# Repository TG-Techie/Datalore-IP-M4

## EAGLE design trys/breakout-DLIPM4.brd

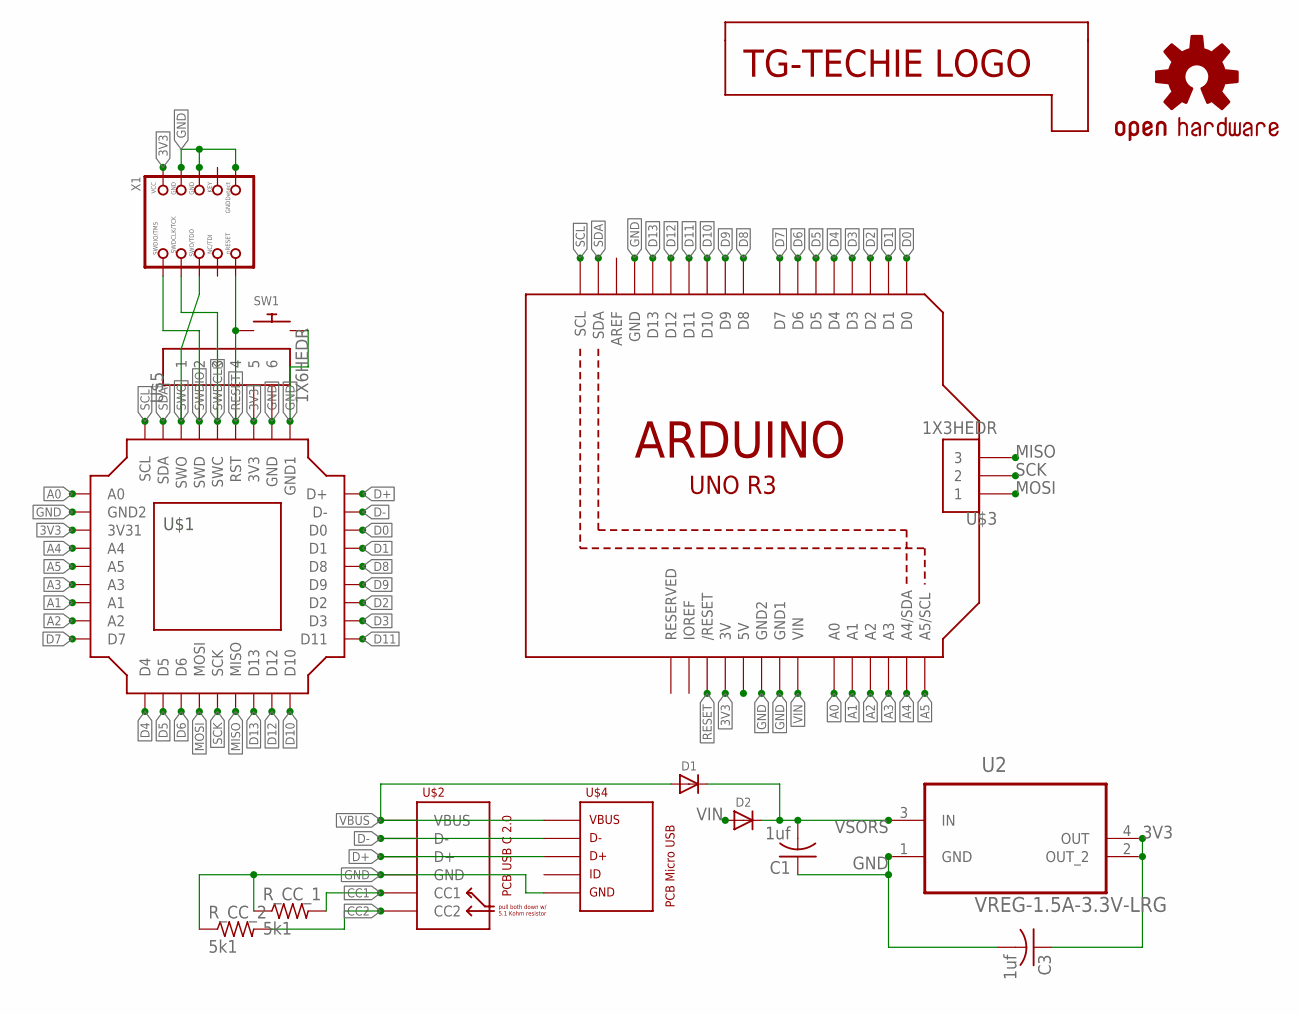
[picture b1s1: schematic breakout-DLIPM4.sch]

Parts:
C1, C3: 1uf; TG-C0805MP
D1, D2: DIODESOD-123; SOD-123
LOGO1: OSHW-LOGOS; OSHW-LOGO-S
R_CC_1, R_CC_2: 5k1; TG-R0805
SW1: SWITCH_PUSHBUTTONEVQ-PE; TACT_PANA-EVQ
U1: ARDUINOR3-DIMENSION; ARDUINOR3
U2: VREG-1.5A-3.3V-LRG; SOT230P700X180-4N
U$1: DATALORE-IP-M4; DL_IP_36-.1IN-FOOTPRINT
U$2: USB-C-PCB-USB-2.0-TYPE-CDS_2; USB_TYPE_C_DS_2
U$3: 1X3HEDR; 1X3_HEDR
U$4: USB-B-PCB-MICRO_BSS_2; USB_TYPE_B_SS_2
U$5: 1X6HEDR; 1X6_HEDR
U$7: LOGO-TG_TECHIEBIG?; LOGO_TG_TEST_LARGE
X1: CON-SWD-JTAG-CORTEXBOXPOSTS; 2X05_1.27MM_BOX_POSTS

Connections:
3V3: C3.1, U1.3V, U2.2 (OUT_2), U2.4 (OUT), U$1.7 (3V3), U$1.34 (3V31), U$5.5, X1.1 (VCC)
A0: U1.A0, U$1.36 (A0)
A1: U1.A1, U$1.30 (A1)
A2: U1.A2, U$1.29 (A2)
A3: U1.A3, U$1.31 (A3)
A4: U1.A4 (A4/SDA), U$1.33 (A4)
A5: U1.A5 (A5/SCL), U$1.32 (A5)
CC1: R_CC_1.2, U$2.A5 (CC1)
CC2: R_CC_2.2, U$2.B5 (CC2)
D0: U1.D0, U$1.12 (D0)
D1: U1.D1, U$1.13 (D1)
D2: U1.D2, U$1.16 (D2)
D3: U1.D3, U$1.17 (D3)
D4: U1.D4, U$1.27 (D4)
D5: U1.D5, U$1.26 (D5)
D6: U1.D6, U$1.25 (D6)
D7: U1.D7, U$1.28 (D7)
D8: U1.D8, U$1.14 (D8)
D9: U1.D9, U$1.15 (D9)
D10: U1.D10, U$1.19 (D10)
D11: U1.D11, U$1.18 (D11)
D12: U1.D12, U$1.20 (D12)
D13: U1.D13, U$1.21 (D13)
D+: U$1.10 (D+), U$2.A6 (D+), U$2.B6 (D+), U$4.3
D-: U$1.11 (D-), U$2.A7 (D-), U$2.B7 (D-), U$4.2
GND: C1.1, C3.2, R_CC_1.1, R_CC_2.1, SW1.P$2, U1.GND, U1.GND1, U1.GND2, U2.1 (GND), U$1.8 (GND), U$1.9 (GND1), U$1.35 (GND2), U$2.A1 (GND), U$2.A12 (GND), U$2.B1 (GND), U$2.B12 (GND), U$4.5, U$5.6, X1.3 (GND), X1.5 (GND), X1.9 (GNDDETECT)
MISO: U$1.22 (MISO), U$3.3
MOSI: U$1.24 (MOSI), U$3.1
RESET: SW1.P$1, U1.RESET (/RESET), U$1.6 (RST), U$5.4, X1.10 (NRESET)
SCK: U$1.23 (SCK), U$3.2
SCL: U1.SCL, U$1.1 (SCL)
SDA: U1.SDA, U$1.2 (SDA)
SWDCLK: U$1.5 (SWC), U$5.3, X1.4 (SWDCLK)
SWDIO: U$1.4 (SWD), U$5.2, X1.2 (SWDIO)
SWO: U$1.3 (SWO), U$5.1, X1.6 (SWO)
VBUS: D1.A, U$2.A4 (VBUS), U$2.A9 (VBUS), U$2.B4 (VBUS), U$2.B9 (VBUS), U$4.1
VIN: D2.A, U1.VIN
VSORS: C1.2, D1.C, D2.C, U2.3 (IN)

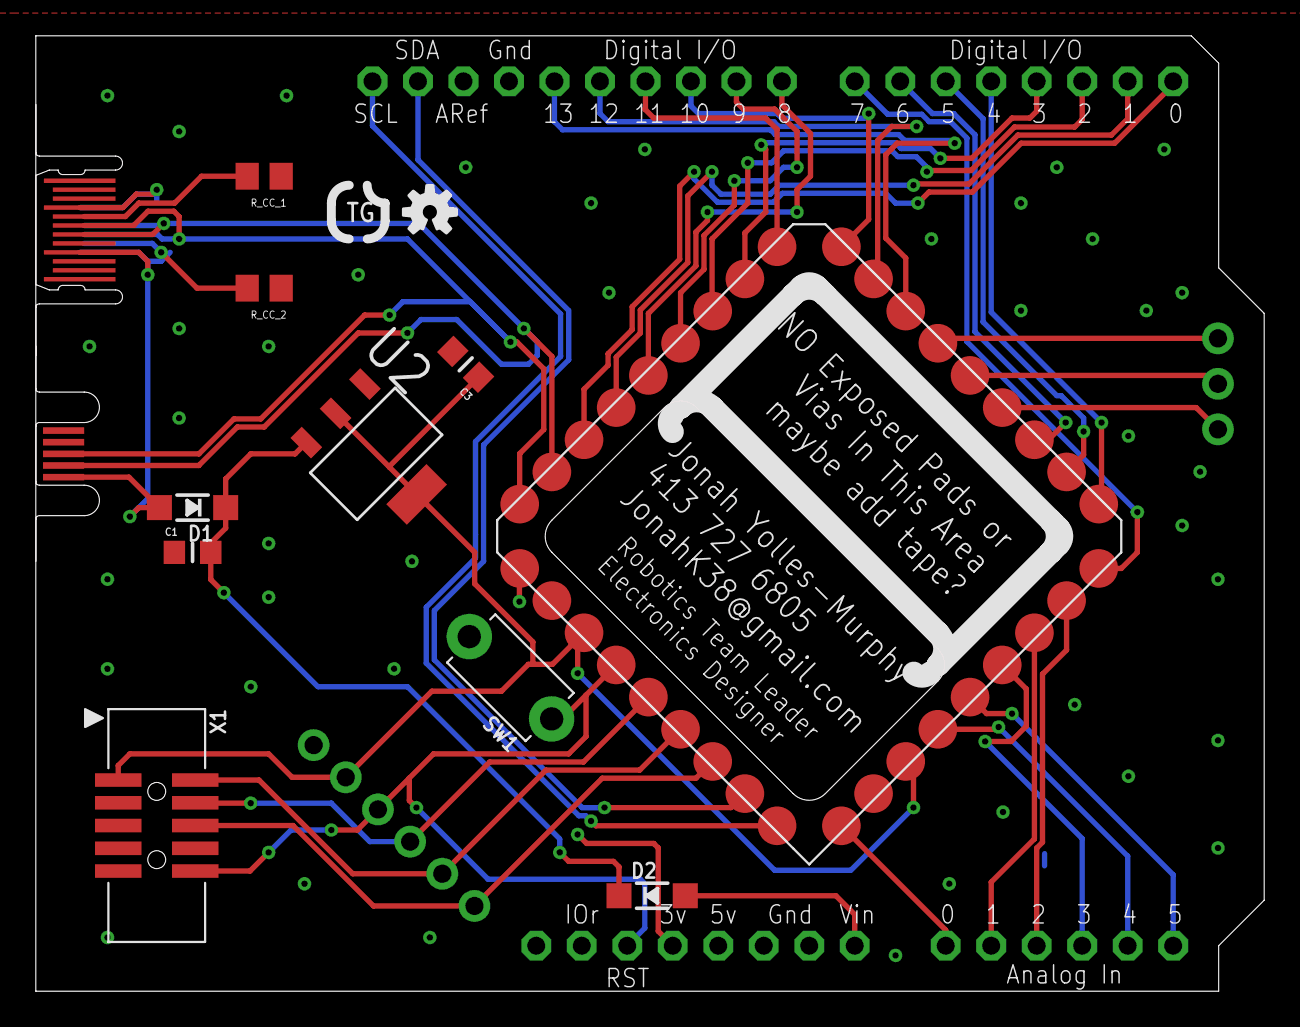
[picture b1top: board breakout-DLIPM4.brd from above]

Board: 2 copper layers, 68.6 x 53.3 mm, 17 parts (0 on the bottom side), 38 nets.

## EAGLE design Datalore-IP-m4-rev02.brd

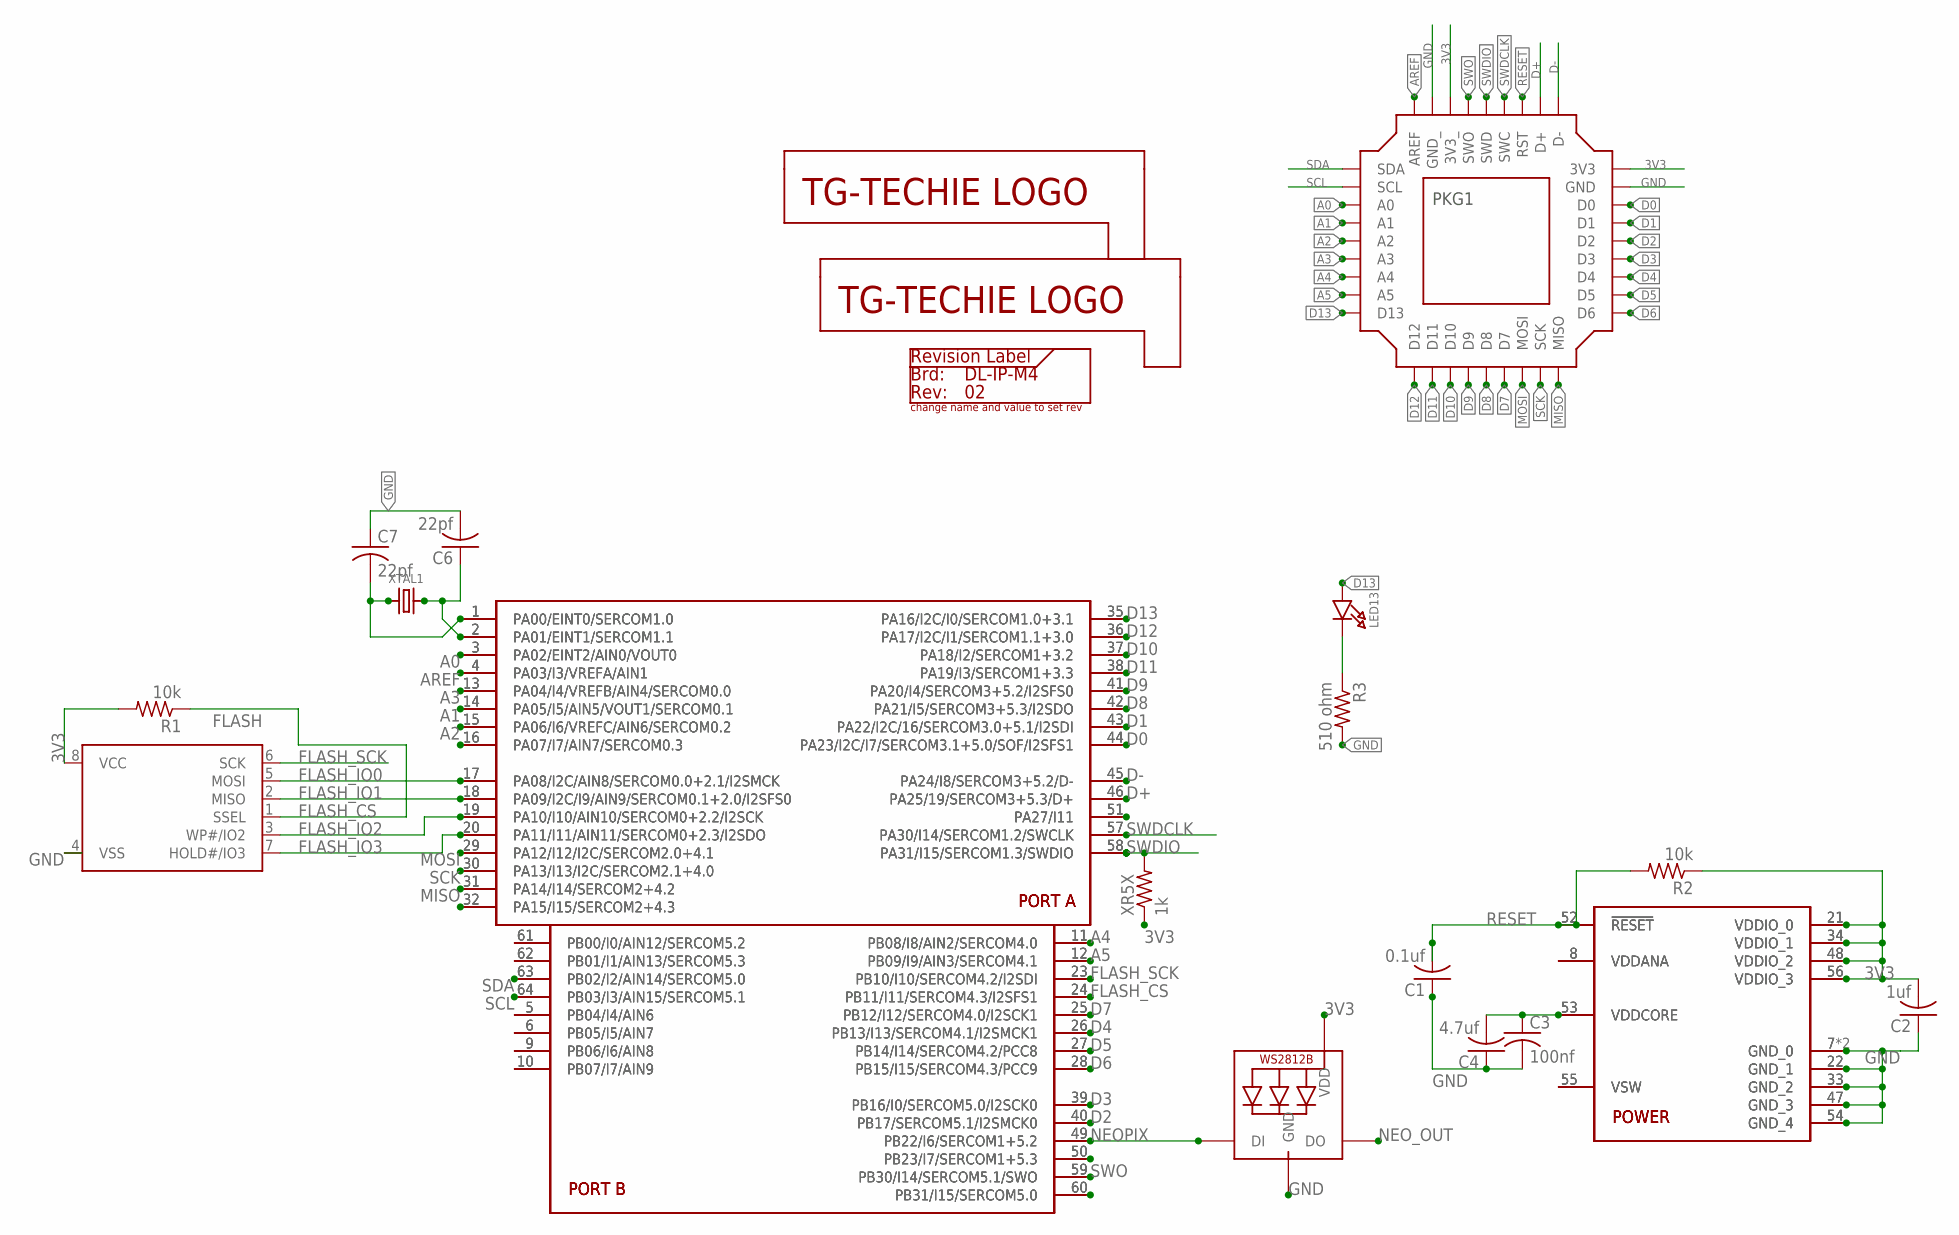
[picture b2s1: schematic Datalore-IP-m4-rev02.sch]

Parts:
..: MCU-ATSAMD51J-ADA+TG_TQFP; QFP50P1200X1200X120-64N
C1: 0.1uf; TG-0603
C2: 1uf; TG-0603
C3: 100nf; TG-0603
C4: 4.7uf; TG-0603
C6, C7: 22pf; TG-0603
DL-IP-M4: 02; REVISION_LABEL
FLASH: FLASH-SPI-CIRCUIT_PYTHON150MIL; SOIC8_150MIL
LED1: LED-NEO-WS2812B3535; LED3535
LED13: LED-MICROBUILDER1206_NOOUTLINE; MICROBUILDER_CHIPLED_1206_NOOUTLINE
PKG1: DATALORE_IP_M4PACKAGE; DL_IP_36-100MIL-PACKAGE
R1, R2: 10k; TG-0603
R3: 510 ohm; TG-0603
U$1, U$5: LOGO-TG_TECHIEBIG?; LOGO_TG_TEST_LARGE
U$3: MCU-ATSAMD51J-ADA+TG_QFP_ADA; MICROBUILDER_PQFN64-1
XR5X: 1k; TG-0603
XTAL1: XTAL_ADA4.9X1.8; MICROBUILDER_CRYSTAL_4.9X1.8

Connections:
3V3: ...21 (VDDIO_0), ...34 (VDDIO_1), ...48 (VDDIO_2), ...56 (VDDIO_3), C2.2, FLASH.8 (VCC), LED1.2 (VDD), PKG1.3 (3V3_), PKG1.10 (3V3), R1.2, R2.1, U$3.21 (VDDIO_0), U$3.34 (VDDIO_1), U$3.48 (VDDIO_2), U$3.56 (VDDIO_3), XR5X.1
A0: ...3 (PA02/EINT2/AIN0/VOUT0), PKG1.34 (A0), U$3.3 (PA02/EINT2/AIN0/VOUT0)
A1: ...14 (PA05/I5/AIN5/VOUT1/SERCOM0.1), PKG1.33 (A1), U$3.14 (PA05/I5/AIN5/VOUT1/SERCOM0.1)
A2: ...15 (PA06/I6/VREFC/AIN6/SERCOM0.2), PKG1.32 (A2), U$3.15 (PA06/I6/VREFC/AIN6/SERCOM0.2)
A3: ...13 (PA04/I4/VREFB/AIN4/SERCOM0.0), PKG1.31 (A3), U$3.13 (PA04/I4/VREFB/AIN4/SERCOM0.0)
A4: ...11 (PB08/I8/AIN2/SERCOM4.0), PKG1.30 (A4), U$3.11 (PB08/I8/AIN2/SERCOM4.0)
A5: ...12 (PB09/I9/AIN3/SERCOM4.1), PKG1.29 (A5), U$3.12 (PB09/I9/AIN3/SERCOM4.1)
AREF: ...4 (PA03/I3/VREFA/AIN1), PKG1.1 (AREF), U$3.4 (PA03/I3/VREFA/AIN1)
D0: ...44 (PA23/I2C/I7/SERCOM3.1+5.0/SOF/I2SFS1), PKG1.12 (D0), U$3.44 (PA23/I2C/I7/SERCOM3.1+5.0/SOF/I2SFS1)
D1: ...43 (PA22/I2C/16/SERCOM3.0+5.1/I2SDI), PKG1.13 (D1), U$3.43 (PA22/I2C/16/SERCOM3.0+5.1/I2SDI)
D2: ...40 (PB17/SERCOM5.1/I2SMCK0), PKG1.14 (D2), U$3.40 (PB17/SERCOM5.1/I2SMCK0)
D3: ...39 (PB16/I0/SERCOM5.0/I2SCK0), PKG1.15 (D3), U$3.39 (PB16/I0/SERCOM5.0/I2SCK0)
D4: ...26 (PB13/I13/SERCOM4.1/I2SMCK1), PKG1.16 (D4), U$3.26 (PB13/I13/SERCOM4.1/I2SMCK1)
D5: ...27 (PB14/I14/SERCOM4.2/PCC8), PKG1.17 (D5), U$3.27 (PB14/I14/SERCOM4.2/PCC8)
D6: ...28 (PB15/I15/SERCOM4.3/PCC9), PKG1.18 (D6), U$3.28 (PB15/I15/SERCOM4.3/PCC9)
D7: ...25 (PB12/I12/SERCOM4.0/I2SCK1), PKG1.22 (D7), U$3.25 (PB12/I12/SERCOM4.0/I2SCK1)
D8: ...42 (PA21/I5/SERCOM3+5.3/I2SDO), PKG1.23 (D8), U$3.42 (PA21/I5/SERCOM3+5.3/I2SDO)
D9: ...41 (PA20/I4/SERCOM3+5.2/I2SFS0), PKG1.24 (D9), U$3.41 (PA20/I4/SERCOM3+5.2/I2SFS0)
D10: ...37 (PA18/I2/SERCOM1+3.2), PKG1.25 (D10), U$3.37 (PA18/I2/SERCOM1+3.2)
D11: ...38 (PA19/I3/SERCOM1+3.3), PKG1.26 (D11), U$3.38 (PA19/I3/SERCOM1+3.3)
D12: ...36 (PA17/I2C/I1/SERCOM1.1+3.0), PKG1.27 (D12), U$3.36 (PA17/I2C/I1/SERCOM1.1+3.0)
D13: ...35 (PA16/I2C/I0/SERCOM1.0+3.1), LED13.A, PKG1.28 (D13), U$3.35 (PA16/I2C/I0/SERCOM1.0+3.1)
D+: ...46 (PA25/19/SERCOM3+5.3/D+), PKG1.8 (D+), U$3.46 (PA25/19/SERCOM3+5.3/D+)
D-: ...45 (PA24/I8/SERCOM3+5.2/D-), PKG1.9 (D-), U$3.45 (PA24/I8/SERCOM3+5.2/D-)
FLASH_CS: ...24 (PB11/I11/SERCOM4.3/I2SFS1), FLASH.1 (SSEL), R1.1, U$3.24 (PB11/I11/SERCOM4.3/I2SFS1)
FLASH_IO0: ...17 (PA08/I2C/AIN8/SERCOM0.0+2.1/I2SMCK), FLASH.5 (MOSI), U$3.17 (PA08/I2C/AIN8/SERCOM0.0+2.1/I2SMCK)
FLASH_IO1: ...18 (PA09/I2C/I9/AIN9/SERCOM0.1+2.0/I2SFS0), FLASH.2 (MISO), U$3.18 (PA09/I2C/I9/AIN9/SERCOM0.1+2.0/I2SFS0)
FLASH_IO2: ...19 (PA10/I10/AIN10/SERCOM0+2.2/I2SCK), FLASH.3 (WP#/IO2), U$3.19 (PA10/I10/AIN10/SERCOM0+2.2/I2SCK)
FLASH_IO3: ...20 (PA11/I11/AIN11/SERCOM0+2.3/I2SDO), FLASH.7 (HOLD#/IO3), U$3.20 (PA11/I11/AIN11/SERCOM0+2.3/I2SDO)
FLASH_SCK: ...23 (PB10/I10/SERCOM4.2/I2SDI), FLASH.6 (SCK), U$3.23 (PB10/I10/SERCOM4.2/I2SDI)
GND: ...7 (GND_0), ...22 (GND_1), ...33 (GND_2), ...47 (GND_3), ...54 (GND_4), C1.1, C2.1, C3.2, C4.1, C6.2, C7.1, FLASH.4 (VSS), LED1.4 (GND), PKG1.2 (GND_), PKG1.11 (GND), R3.2, U$3.7 (GND_0), U$3.22 (GND_1), U$3.33 (GND_2), U$3.47 (GND_3), U$3.54 (GND_4), U$3.EXP (GND_0)
MISO: ...31 (PA14/I14/SERCOM2+4.2), PKG1.19 (MISO), U$3.31 (PA14/I14/SERCOM2+4.2)
MOSI: ...29 (PA12/I12/I2C/SERCOM2.0+4.1), PKG1.21 (MOSI), U$3.29 (PA12/I12/I2C/SERCOM2.0+4.1)
unnamed: ...16 (PA07/I7/AIN7/SERCOM0.3), U$3.16 (PA07/I7/AIN7/SERCOM0.3)
unnamed: ...32 (PA15/I15/SERCOM2+4.3), U$3.32 (PA15/I15/SERCOM2+4.3)
unnamed: ...51 (PA27/I11), U$3.51 (PA27/I11)
unnamed: LED13.C, R3.1
unnamed: ...8 (VDDANA), U$3.8 (VDDANA)
unnamed: ...55 (VSW), U$3.55 (VSW)
unnamed: ...61 (PB00/I0/AIN12/SERCOM5.2), U$3.61 (PB00/I0/AIN12/SERCOM5.2)
unnamed: ...62 (PB01/I1/AIN13/SERCOM5.3), U$3.62 (PB01/I1/AIN13/SERCOM5.3)
unnamed: ...5 (PB04/I4/AIN6), U$3.5 (PB04/I4/AIN6)
unnamed: ...50 (PB23/I7/SERCOM1+5.3), U$3.50 (PB23/I7/SERCOM1+5.3)
unnamed: ...60 (PB31/I15/SERCOM5.0), U$3.60 (PB31/I15/SERCOM5.0)
unnamed: ...6 (PB05/I5/AIN7), U$3.6 (PB05/I5/AIN7)
unnamed: ...9 (PB06/I6/AIN8), U$3.9 (PB06/I6/AIN8)
unnamed: ...10 (PB07/I7/AIN9), U$3.10 (PB07/I7/AIN9)
NEOPIX: ...49 (PB22/I6/SERCOM1+5.2), LED1.1 (DI), U$3.49 (PB22/I6/SERCOM1+5.2)
NEO_OUT: LED1.3 (DO)
RESET: ...52 (!RESET), C1.2, PKG1.7 (RST), R2.2, U$3.52 (!RESET)
SCK: ...30 (PA13/I13/I2C/SERCOM2.1+4.0), PKG1.20 (SCK), U$3.30 (PA13/I13/I2C/SERCOM2.1+4.0)
SCL: ...64 (PB03/I3/AIN15/SERCOM5.1), PKG1.35 (SCL), U$3.64 (PB03/I3/AIN15/SERCOM5.1)
SDA: ...63 (PB02/I2/AIN14/SERCOM5.0), PKG1.36 (SDA), U$3.63 (PB02/I2/AIN14/SERCOM5.0)
SWDCLK: ...57 (PA30/I14/SERCOM1.2/SWCLK), PKG1.6 (SWC), U$3.57 (PA30/I14/SERCOM1.2/SWCLK)
SWDIO: ...58 (PA31/I15/SERCOM1.3/SWDIO), PKG1.5 (SWD), U$3.58 (PA31/I15/SERCOM1.3/SWDIO), XR5X.2
SWO: ...59 (PB30/I14/SERCOM5.1/SWO), PKG1.4 (SWO), U$3.59 (PB30/I14/SERCOM5.1/SWO)
VCORE: ...53 (VDDCORE), C3.1, C4.2, U$3.53 (VDDCORE)
XTAL0: ...2 (PA01/EINT1/SERCOM1.1), C6.1, U$3.2 (PA01/EINT1/SERCOM1.1), XTAL1.2
XTAL1: ...1 (PA00/EINT0/SERCOM1.0), C7.2, U$3.1 (PA00/EINT0/SERCOM1.0), XTAL1.1

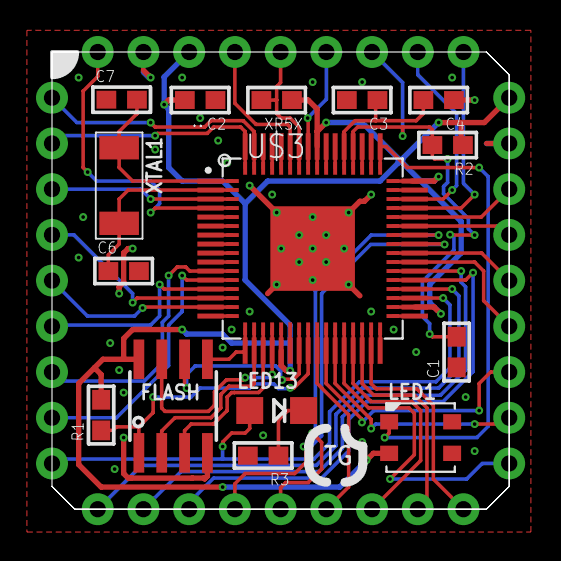
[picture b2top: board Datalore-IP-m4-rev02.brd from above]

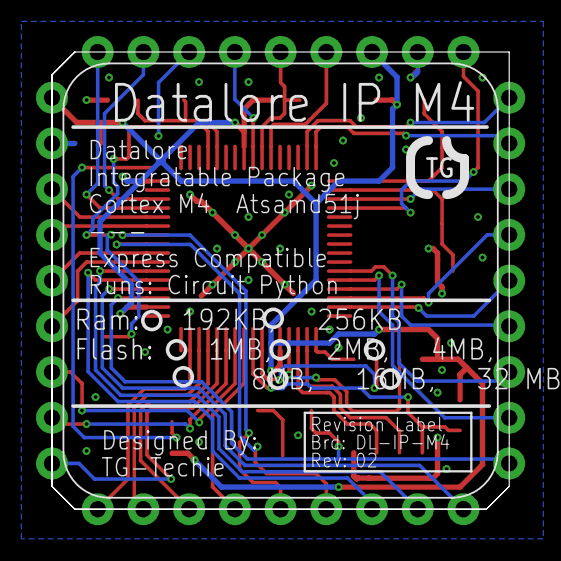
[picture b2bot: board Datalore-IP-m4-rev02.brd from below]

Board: 2 copper layers, 25.4 x 25.4 mm, 20 parts (2 on the bottom side), 58 nets.

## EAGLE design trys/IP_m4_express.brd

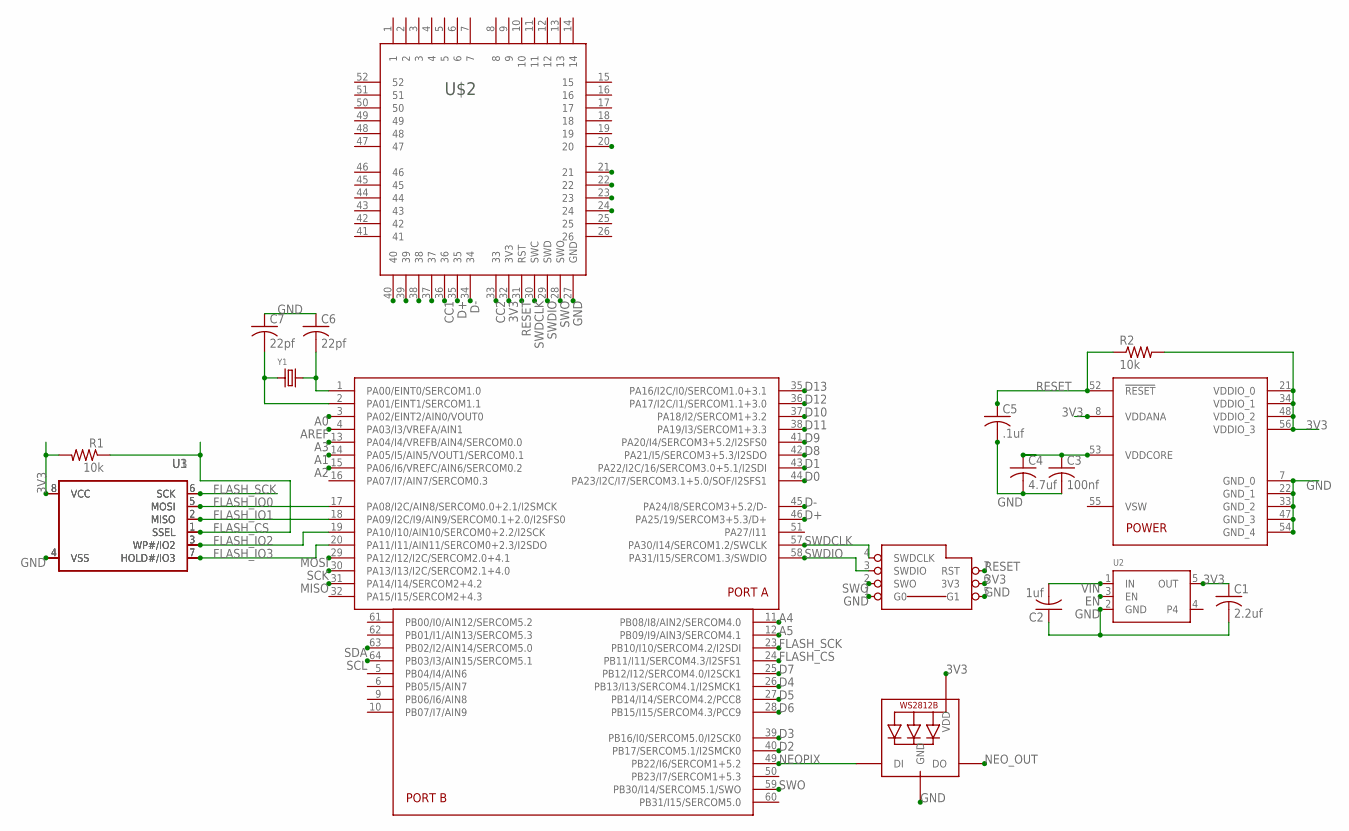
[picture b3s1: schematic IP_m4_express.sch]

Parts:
C1: 2.2uf; TG-C0805MP
C2: 1uf; TG-C0805MP
C3: 100nf; TG-C0805MP
C4: 4.7uf; TG-C0805MP
C5: .1uf; TG-C0805MP
C6, C7: 22pf; TG-C0805MP
LED1: LED-NEO-WS2812B3535; LED3535
R1, R2: 10k; TG-R0805
U1: FLASH-SPI-SOIC8; SOIC8_150MIL
U2: VREG_STD_MIN_SOT23-5; SOT23-5
U3: FLASH-SPI-SOIC8208MIL; SOIC8_208MIL
U$1: MCU-ATSAMD51J-ADATQFP; QFP50P1200X1200X120-64N
U$2: DL_IP-52PACKAGE; DL_IP-52_2MM-25X30-PACKAGE
U$3: SWD_POGO
Y1: XTAL_ADA4.9X1.8; MICROBUILDER_CRYSTAL_4.9X1.8

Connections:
3V3: C1.1, LED1.2 (VDD), R1.2, R2.2, U1.8 (VCC), U2.5 (OUT), U3.8 (VCC), U$1.8 (VDDANA), U$1.21 (VDDIO_0), U$1.34 (VDDIO_1), U$1.48 (VDDIO_2), U$1.56 (VDDIO_3), U$2.24, U$2.32 (3V3), U$3.6 (3V3)
A0: U$1.3 (PA02/EINT2/AIN0/VOUT0)
A1: U$1.14 (PA05/I5/AIN5/VOUT1/SERCOM0.1)
A2: U$1.15 (PA06/I6/VREFC/AIN6/SERCOM0.2)
A3: U$1.13 (PA04/I4/VREFB/AIN4/SERCOM0.0)
A4: U$1.11 (PB08/I8/AIN2/SERCOM4.0)
A5: U$1.12 (PB09/I9/AIN3/SERCOM4.1)
AREF: U$1.4 (PA03/I3/VREFA/AIN1)
CC1: U$2.36
CC2: U$2.33
D0: U$1.44 (PA23/I2C/I7/SERCOM3.1+5.0/SOF/I2SFS1)
D1: U$1.43 (PA22/I2C/16/SERCOM3.0+5.1/I2SDI)
D2: U$1.40 (PB17/SERCOM5.1/I2SMCK0)
D3: U$1.39 (PB16/I0/SERCOM5.0/I2SCK0)
D4: U$1.26 (PB13/I13/SERCOM4.1/I2SMCK1)
D5: U$1.27 (PB14/I14/SERCOM4.2/PCC8)
D6: U$1.28 (PB15/I15/SERCOM4.3/PCC9)
D7: U$1.25 (PB12/I12/SERCOM4.0/I2SCK1)
D8: U$1.42 (PA21/I5/SERCOM3+5.3/I2SDO)
D9: U$1.41 (PA20/I4/SERCOM3+5.2/I2SFS0)
D10: U$1.37 (PA18/I2/SERCOM1+3.2)
D11: U$1.38 (PA19/I3/SERCOM1+3.3)
D12: U$1.36 (PA17/I2C/I1/SERCOM1.1+3.0)
D13: U$1.35 (PA16/I2C/I0/SERCOM1.0+3.1)
D+: U$1.46 (PA25/19/SERCOM3+5.3/D+), U$2.35
D-: U$1.45 (PA24/I8/SERCOM3+5.2/D-), U$2.34
EN: U2.3 (EN)
FLASH_CS: R1.1, U1.1 (SSEL), U3.1 (SSEL), U$1.24 (PB11/I11/SERCOM4.3/I2SFS1)
FLASH_IO0: U1.5 (MOSI), U3.5 (MOSI), U$1.17 (PA08/I2C/AIN8/SERCOM0.0+2.1/I2SMCK)
FLASH_IO1: U1.2 (MISO), U3.2 (MISO), U$1.18 (PA09/I2C/I9/AIN9/SERCOM0.1+2.0/I2SFS0)
FLASH_IO2: U1.3 (WP#/IO2), U3.3 (WP#/IO2), U$1.19 (PA10/I10/AIN10/SERCOM0+2.2/I2SCK)
FLASH_IO3: U1.7 (HOLD#/IO3), U3.7 (HOLD#/IO3), U$1.20 (PA11/I11/AIN11/SERCOM0+2.3/I2SDO)
FLASH_SCK: U1.6 (SCK), U3.6 (SCK), U$1.23 (PB10/I10/SERCOM4.2/I2SDI)
GND: C1.2, C2.1, C3.2, C4.2, C5.2, C6.1, C7.1, LED1.4 (GND), U1.4 (VSS), U2.2 (GND), U3.4 (VSS), U$1.7 (GND_0), U$1.22 (GND_1), U$1.33 (GND_2), U$1.47 (GND_3), U$1.54 (GND_4), U$2.27 (GND), U$3.1 (G0), U$3.5 (G1)
MISO: U$1.31 (PA14/I14/SERCOM2+4.2)
MOSI: U$1.29 (PA12/I12/I2C/SERCOM2.0+4.1)
unnamed: C7.2, U$1.2 (PA01/EINT1/SERCOM1.1), Y1.1
unnamed: C6.2, U$1.1 (PA00/EINT0/SERCOM1.0), Y1.2
NEOPIX: LED1.1 (DI), U$1.49 (PB22/I6/SERCOM1+5.2)
NEO_OUT: LED1.3 (DO)
RESET: C5.1, R2.1, U$1.52 (!RESET), U$2.31 (RST), U$3.7 (RST)
SCK: U$1.30 (PA13/I13/I2C/SERCOM2.1+4.0)
SCL: U$1.64 (PB03/I3/AIN15/SERCOM5.1)
SDA: U$1.63 (PB02/I2/AIN14/SERCOM5.0)
SWDCLK: U$1.57 (PA30/I14/SERCOM1.2/SWCLK), U$2.30 (SWC), U$3.4 (SWDCLK)
SWDIO: U$1.58 (PA31/I15/SERCOM1.3/SWDIO), U$2.29 (SWD), U$3.3 (SWDIO)
SWO: U$1.59 (PB30/I14/SERCOM5.1/SWO), U$2.28 (SWO), U$3.2 (SWO)
VCORE: C3.1, C4.1, U$1.53 (VDDCORE)
VIN: C2.2, U2.1 (IN)

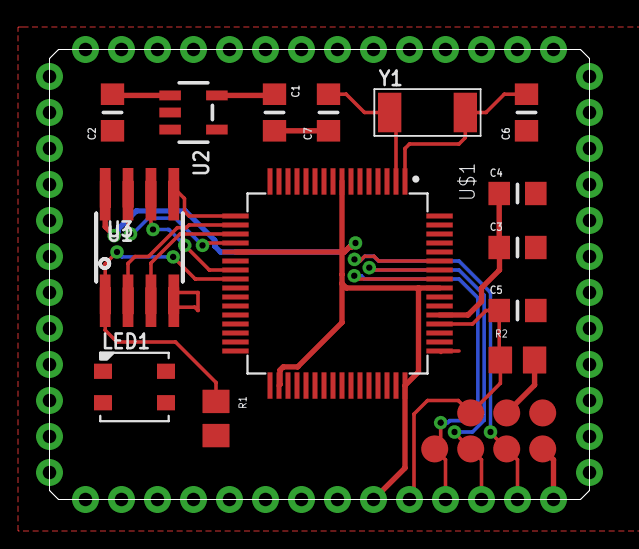
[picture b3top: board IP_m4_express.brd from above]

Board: 2 copper layers, 30.0 x 25.0 mm, 17 parts (0 on the bottom side), 19 nets.

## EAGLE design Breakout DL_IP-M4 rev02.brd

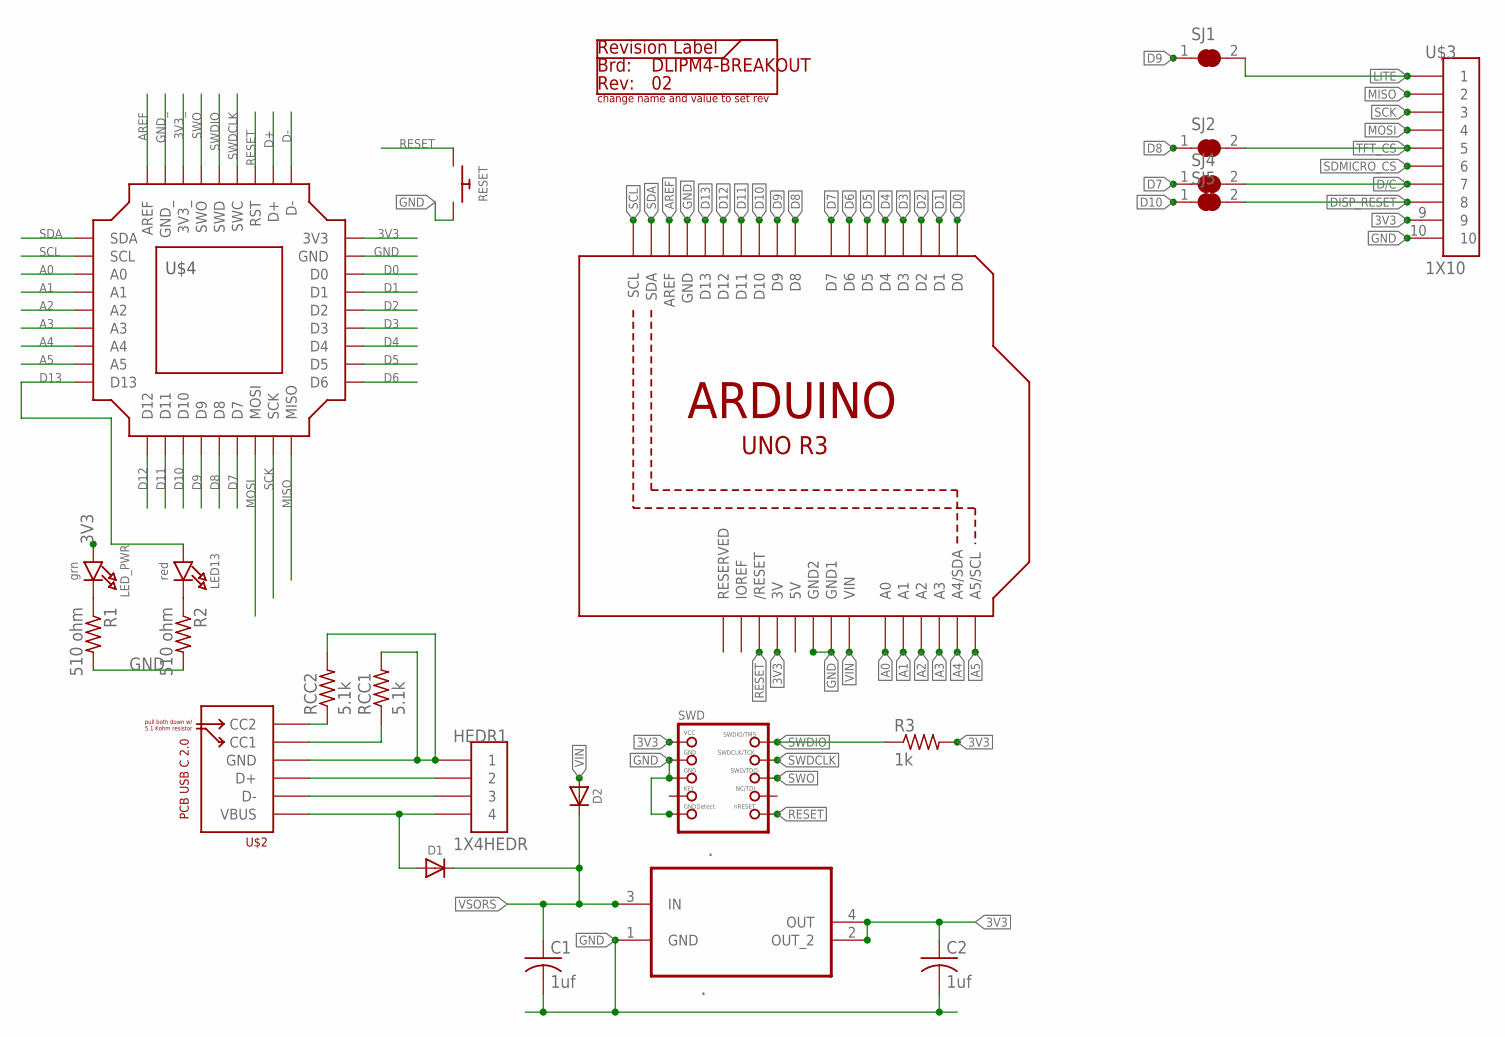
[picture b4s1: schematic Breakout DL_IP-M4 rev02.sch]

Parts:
.: .; SOT230P700X180-4N
C1, C2: 1uf; TG-0603
D1, D2: DIODESOD-123; SOD-123
DLIPM4-BREAKOUT: 02; REVISION_LABEL_LONG
HEDR1: 1X4HEDR; 1X4_HEDR
LED13: red; MICROBUILDER_CHIPLED_1206_NOOUTLINE
LED_PWR: grn; MICROBUILDER_CHIPLED_1206_NOOUTLINE
R1, R2: 510 ohm; TG-0603
R3: 1k; TG-0603
RCC1, RCC2: 5.1k; TG-0603
RESET: SWITCH_PUSHBUTTONEVQ-PE; TACT_PANA-EVQ
SJ1, SJ2, SJ4, SJ5: JUMPER_CLOSEDTEMP; SOLDERJUMPER_CLOSEDWIRE
SWD: CON-SWD-JTAG-CORTEXBOXPOSTS; 2X05_1.27MM_BOX_POSTS
U1: ARDUINOR3-BPLACE
U$2: USB-C-PCB-USB-2.0-TYPE-CDS_2; USB_TYPE_C_DS_2
U$3: 1X10; 1X10_HEDR
U$4: DATALORE_IP_M4FOOTPRINT; DL_IP_36-100MIL-FOOTPRINT

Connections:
3V3: ..2 (OUT_2), ..4 (OUT), C2.1, LED_PWR.A, R3.2, SWD.1 (VCC), U1.3V, U$3.9, U$4.10 (3V3)
3V3_: U$4.3 (3V3_)
5V: U1.5V
A0: U1.A0, U$4.34 (A0)
A1: U1.A1, U$4.33 (A1)
A2: U1.A2, U$4.32 (A2)
A3: U1.A3, U$4.31 (A3)
A4: U1.A4 (A4/SDA), U$4.30 (A4)
A5: U1.A5 (A5/SCL), U$4.29 (A5)
AREF: U1.AREF, U$4.1 (AREF)
CC1: RCC1.1, U$2.A5 (CC1)
CC2: RCC2.1, U$2.B5 (CC2)
D0: U1.D0, U$4.12 (D0)
D1: U1.D1, U$4.13 (D1)
D2: U1.D2, U$4.14 (D2)
D3: U1.D3, U$4.15 (D3)
D4: U1.D4, U$4.16 (D4)
D5: U1.D5, U$4.17 (D5)
D6: U1.D6, U$4.18 (D6)
D7: SJ4.1, U1.D7, U$4.22 (D7)
D8: SJ2.1, U1.D8, U$4.23 (D8)
D9: SJ1.1, U1.D9, U$4.24 (D9)
D10: SJ5.1, U1.D10, U$4.25 (D10)
D11: U1.D11, U$4.26 (D11)
D12: U1.D12, U$4.27 (D12)
D13: LED13.A, U1.D13, U$4.28 (D13)
D+: HEDR1.2, U$2.A6 (D+), U$2.B6 (D+), U$4.8 (D+)
D-: HEDR1.3, U$2.A7 (D-), U$2.B7 (D-), U$4.9 (D-)
D/C: SJ4.2, U$3.7
DISP_RESET: SJ5.2, U$3.8
GND: ..1 (GND), C1.2, C2.2, HEDR1.1, R1.2, R2.2, RCC1.2, RCC2.2, RESET.P$2, SWD.3 (GND), SWD.5 (GND), SWD.9 (GNDDETECT), U1.GND, U1.GND1, U1.GND2, U$2.A1 (GND), U$2.A12 (GND), U$2.B1 (GND), U$2.B12 (GND), U$3.10, U$4.11 (GND)
GND_: U$4.2 (GND_)
LITE: SJ1.2, U$3.1
MISO: U$3.2, U$4.19 (MISO)
MOSI: U$3.4, U$4.21 (MOSI)
unnamed: LED_PWR.C, R1.1
unnamed: LED13.C, R2.1
RESET: RESET.P$1, SWD.10 (NRESET), U1.RESET (/RESET), U$4.7 (RST)
SCK: U$3.3, U$4.20 (SCK)
SCL: U1.SCL, U$4.35 (SCL)
SDA: U1.SDA, U$4.36 (SDA)
SDMICRO_CS: U$3.6
SWDCLK: SWD.4 (SWDCLK), U$4.6 (SWC)
SWDIO: R3.1, SWD.2 (SWDIO), U$4.5 (SWD)
SWO: SWD.6 (SWO), U$4.4 (SWO)
TFT_CS: SJ2.2, U$3.5
VBUS: D1.A, HEDR1.4, U$2.A4 (VBUS), U$2.A9 (VBUS), U$2.B4 (VBUS), U$2.B9 (VBUS)
VIN: D2.A, U1.VIN
VSORS: ..3 (IN), C1.1, D1.C, D2.C

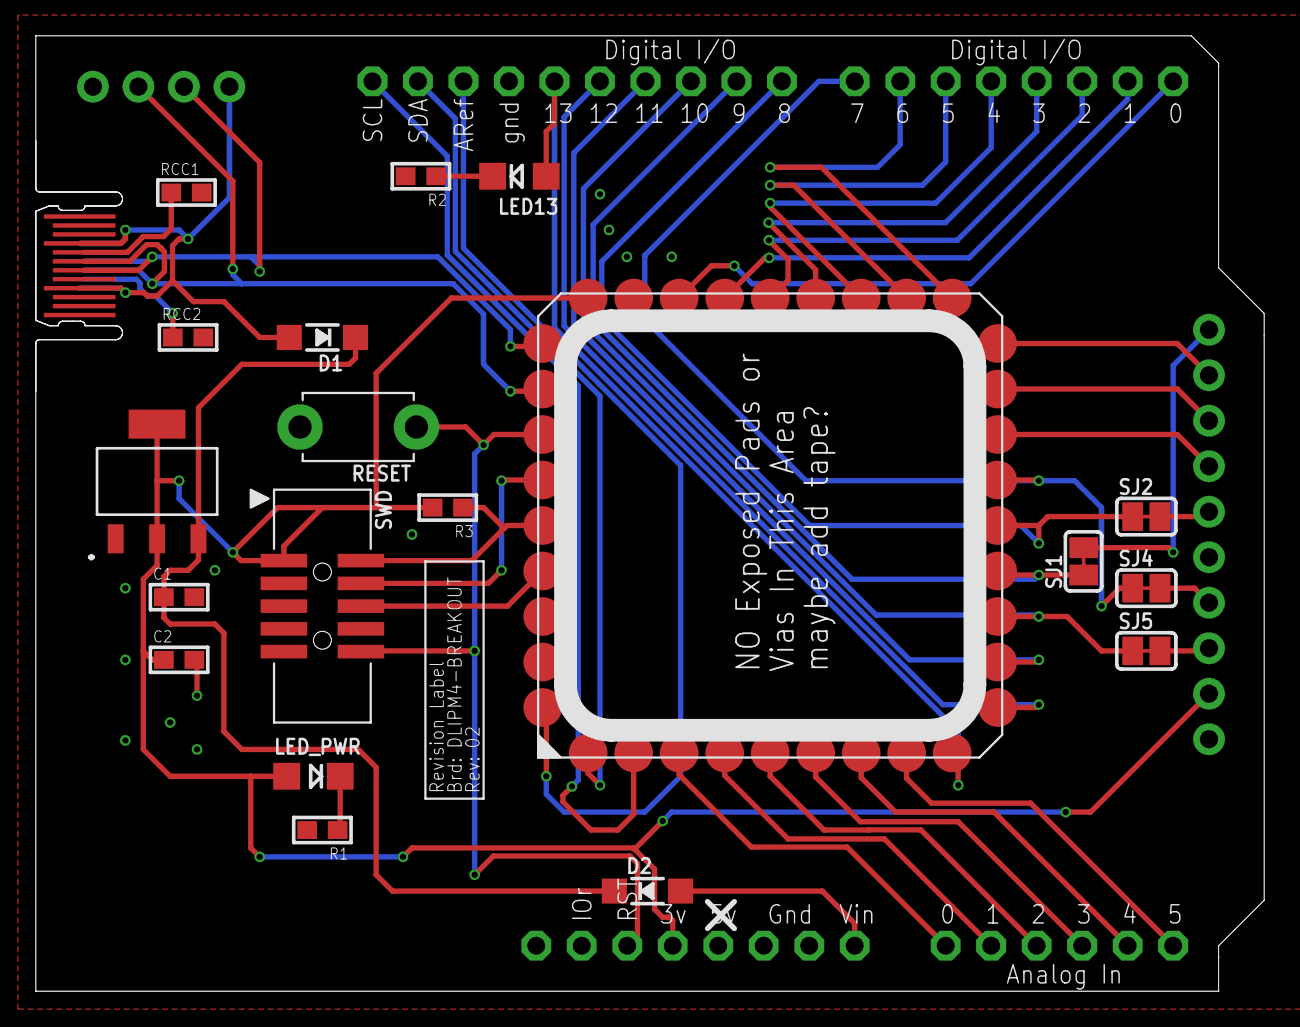
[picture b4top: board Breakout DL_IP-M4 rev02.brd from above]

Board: 2 copper layers, 68.6 x 53.3 mm, 24 parts (0 on the bottom side), 45 nets.

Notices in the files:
parts and their libraries:
SparkFun-Aesthetics: Licensing: Creative Commons ShareAlike 4.0 International - https://creativecommons.org/licenses/by-sa/4.0
